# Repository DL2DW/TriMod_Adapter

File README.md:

# TriMod Adapter

## IEEE-488 for the Commodore 1541 Disk Drive

With the help of this adapter, you can turn a VC1541 into a 2031LP in no time. And it is just as easy to switch back again.

So to speak, the best of two different worlds. Once the Commodore 1541 with the CBM bus for Commodore C64 and C128. And switchable as 2031LP for the PET and CBM world with GPIB (IEEE-488) interface.

The idea came from Andre Fachat and was published in 64'er magazine in the 1980s. He was the first to come up with the idea of turning a 1541 into a 2031LP.

I took up this idea again and even made the whole thing switchable. So you can always use the "1541 mode" again without removing the adapter again.

# Technical

Commodore had derived the 2031LP from the 1541 at that time. If you look at both schematics, they only differ in one detail.

And this is the connection to the outside world. 

On the 1541, the VIA 6522 is only partially used, because port A is not connected. Port B provides the lines for the CBM bus, which communicate with the computer via a 74LS14 and 74LS06 driver.

In contrast, port A is also required for the 2031LP. This provides the 8 parallel data lines, while port B is responsible for the control lines of the GPIB bus. Here the two drivers SN75160 and SN75161 are used.

And these are basically the actual differences, to put it simply.

So the 1541 can be easily converted to a 2031 with an adapter board. Of course, the Kernal has to be exchanged accordingly.

So that the adapter does not have to be removed every time you want to use the CBM bus, I have made the whole switchable.

With the help of CD4066 4-fold switches, the lines can be easily switched. At the same time the integrated Kernal adapter is also switched.

A 27128 EPROM is required for the Kernal. First (address 0x0000) the binary for the 1541 mode is written and afterwards (address 0x2000) the binary for the IEEE-488 mode.

With setting the jumper the mode can be switched. Of course this should be done only in the switched off state.

# BOM

Here is the list of components. 

|      | Description                                                  | Part                  | References           | Value                       | Quantity Per PCB |
| ---- | ------------------------------------------------------------ | --------------------- | -------------------- | --------------------------- | ---------------- |
| 1    | Unpolarized capacitor                                        | C                     | C1 C2 C3 C4 C5 C6 C7 | 100nF                       | 7                |
| 2    | Diode                                                        | D                     | D1 D2                | 1N4148                      | 2                |
| 3    | Generic connector, single row, 01x12, script generated (kicad-library-utils/schlib/autogen/connector/) | Conn_01x12            | J4 J5                | Conn_01x12                  | 2                |
| 4    | Generic connector, double row, 02x12, top/bottom pin numbering scheme (row 1: 1...pins_per_row, row2: pins_per_row+1 ... num_pins), script generated (kicad-library-utils/schlib/autogen/connector/) | Conn_02x12_Top_Bottom | J3                   | IEEE-488 Connector          | 1                |
| 5    | Generic connector, single row, 01x20, script generated (kicad-library-utils/schlib/autogen/connector/) | Conn_01x20            | J1 J2                | PIN Header to PCB 6522 1-20 | 2                |
| 6    | Jumper, 2-pole, open                                         | Jumper_2_Open         | JP1                  | Jumper                      | 1                |
| 7    | Resistor                                                     | R                     | R1 R4                | 10k                         | 2                |
| 8    | Resistor                                                     | R                     | R5                   | 1k                          | 1                |
| 9    | Resistor                                                     | R                     | R2 R3 R6             | 3k3                         | 3                |
| 10   | 2x DIP Switch, Single Pole Single Throw (SPST) switch, small symbol | SW_DIP_x02            | SW1                  | IEEE-488 Device ID          | 1                |
| 11   | OTP EPROM 128 KiBit, [Obsolete 2004-01]                      | 27C128                | U8                   | 27C128                      | 1                |
| 12   | Quad Analog Switches                                         | 4066                  | U1 U2                | 4066                        | 2                |
| 13   |                                                              | 7406N                 | U4                   | 7406N                       | 1                |
| 14   | Quad 2-input XOR                                             | 74LS86                | U3                   | 74LS86                      | 1                |
| 15   |                                                              | MOS6522               | U5                   | MOS6522                     | 1                |
| 16   |                                                              | SN75160               | U6                   | SN75160                     | 1                |
| 17   |                                                              | SN75161               | U7                   | SN75161                     | 1                |

# PCB

The PCB can either be ordered directly from [PCBWay](https://www.pcbway.com/project/shareproject/TriMod_Adapter.html), or you can create it yourself from the Gerber files available here.

If you liked my project, I would be very happy about a small coffee donation.

# License

The contents of this repository, with the exception of the Docs and Software directories, are released under the following license:

- the "Creative Commons Attribution-NonCommercial-ShareAlike 4.0 International License" (CC BY-NC-SA 4.0) full text of this license is included in the [LICENSE.CC-NC-BY-SA-4.0](https://github.com/DL2DW/TriMod_Adapter/blob/main/LICENSE.CC-NC-BY-SA) file and a copy can also be found at https://creativecommons.org/licenses/by-nc-sa/4.0/

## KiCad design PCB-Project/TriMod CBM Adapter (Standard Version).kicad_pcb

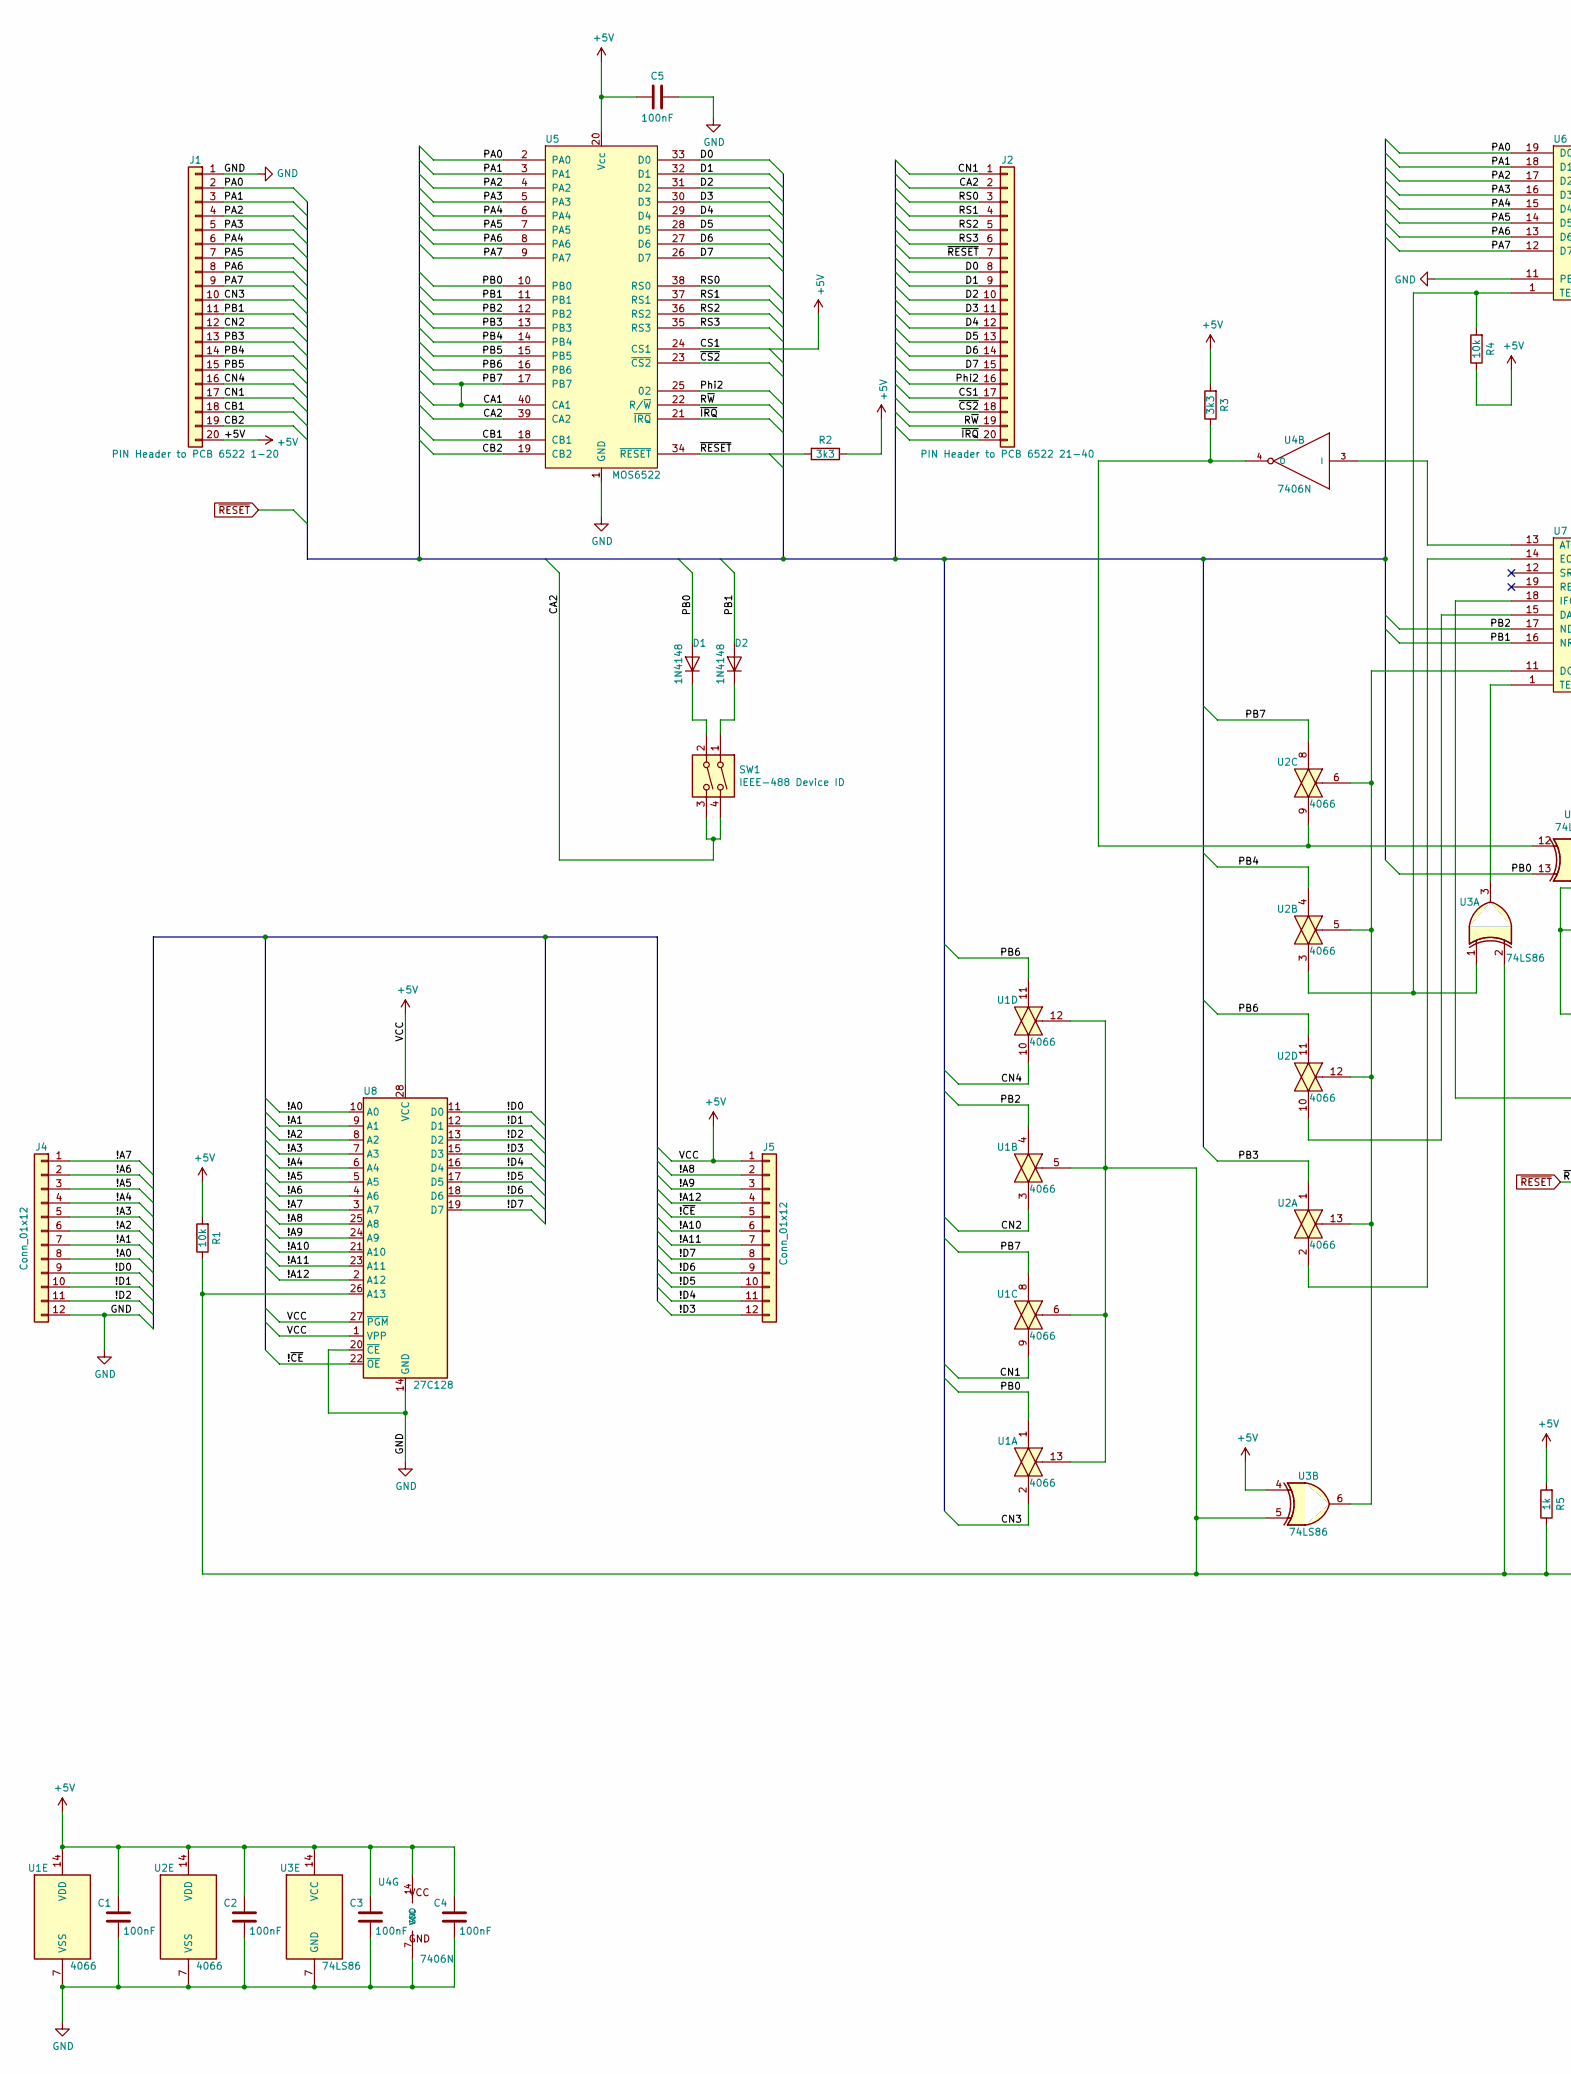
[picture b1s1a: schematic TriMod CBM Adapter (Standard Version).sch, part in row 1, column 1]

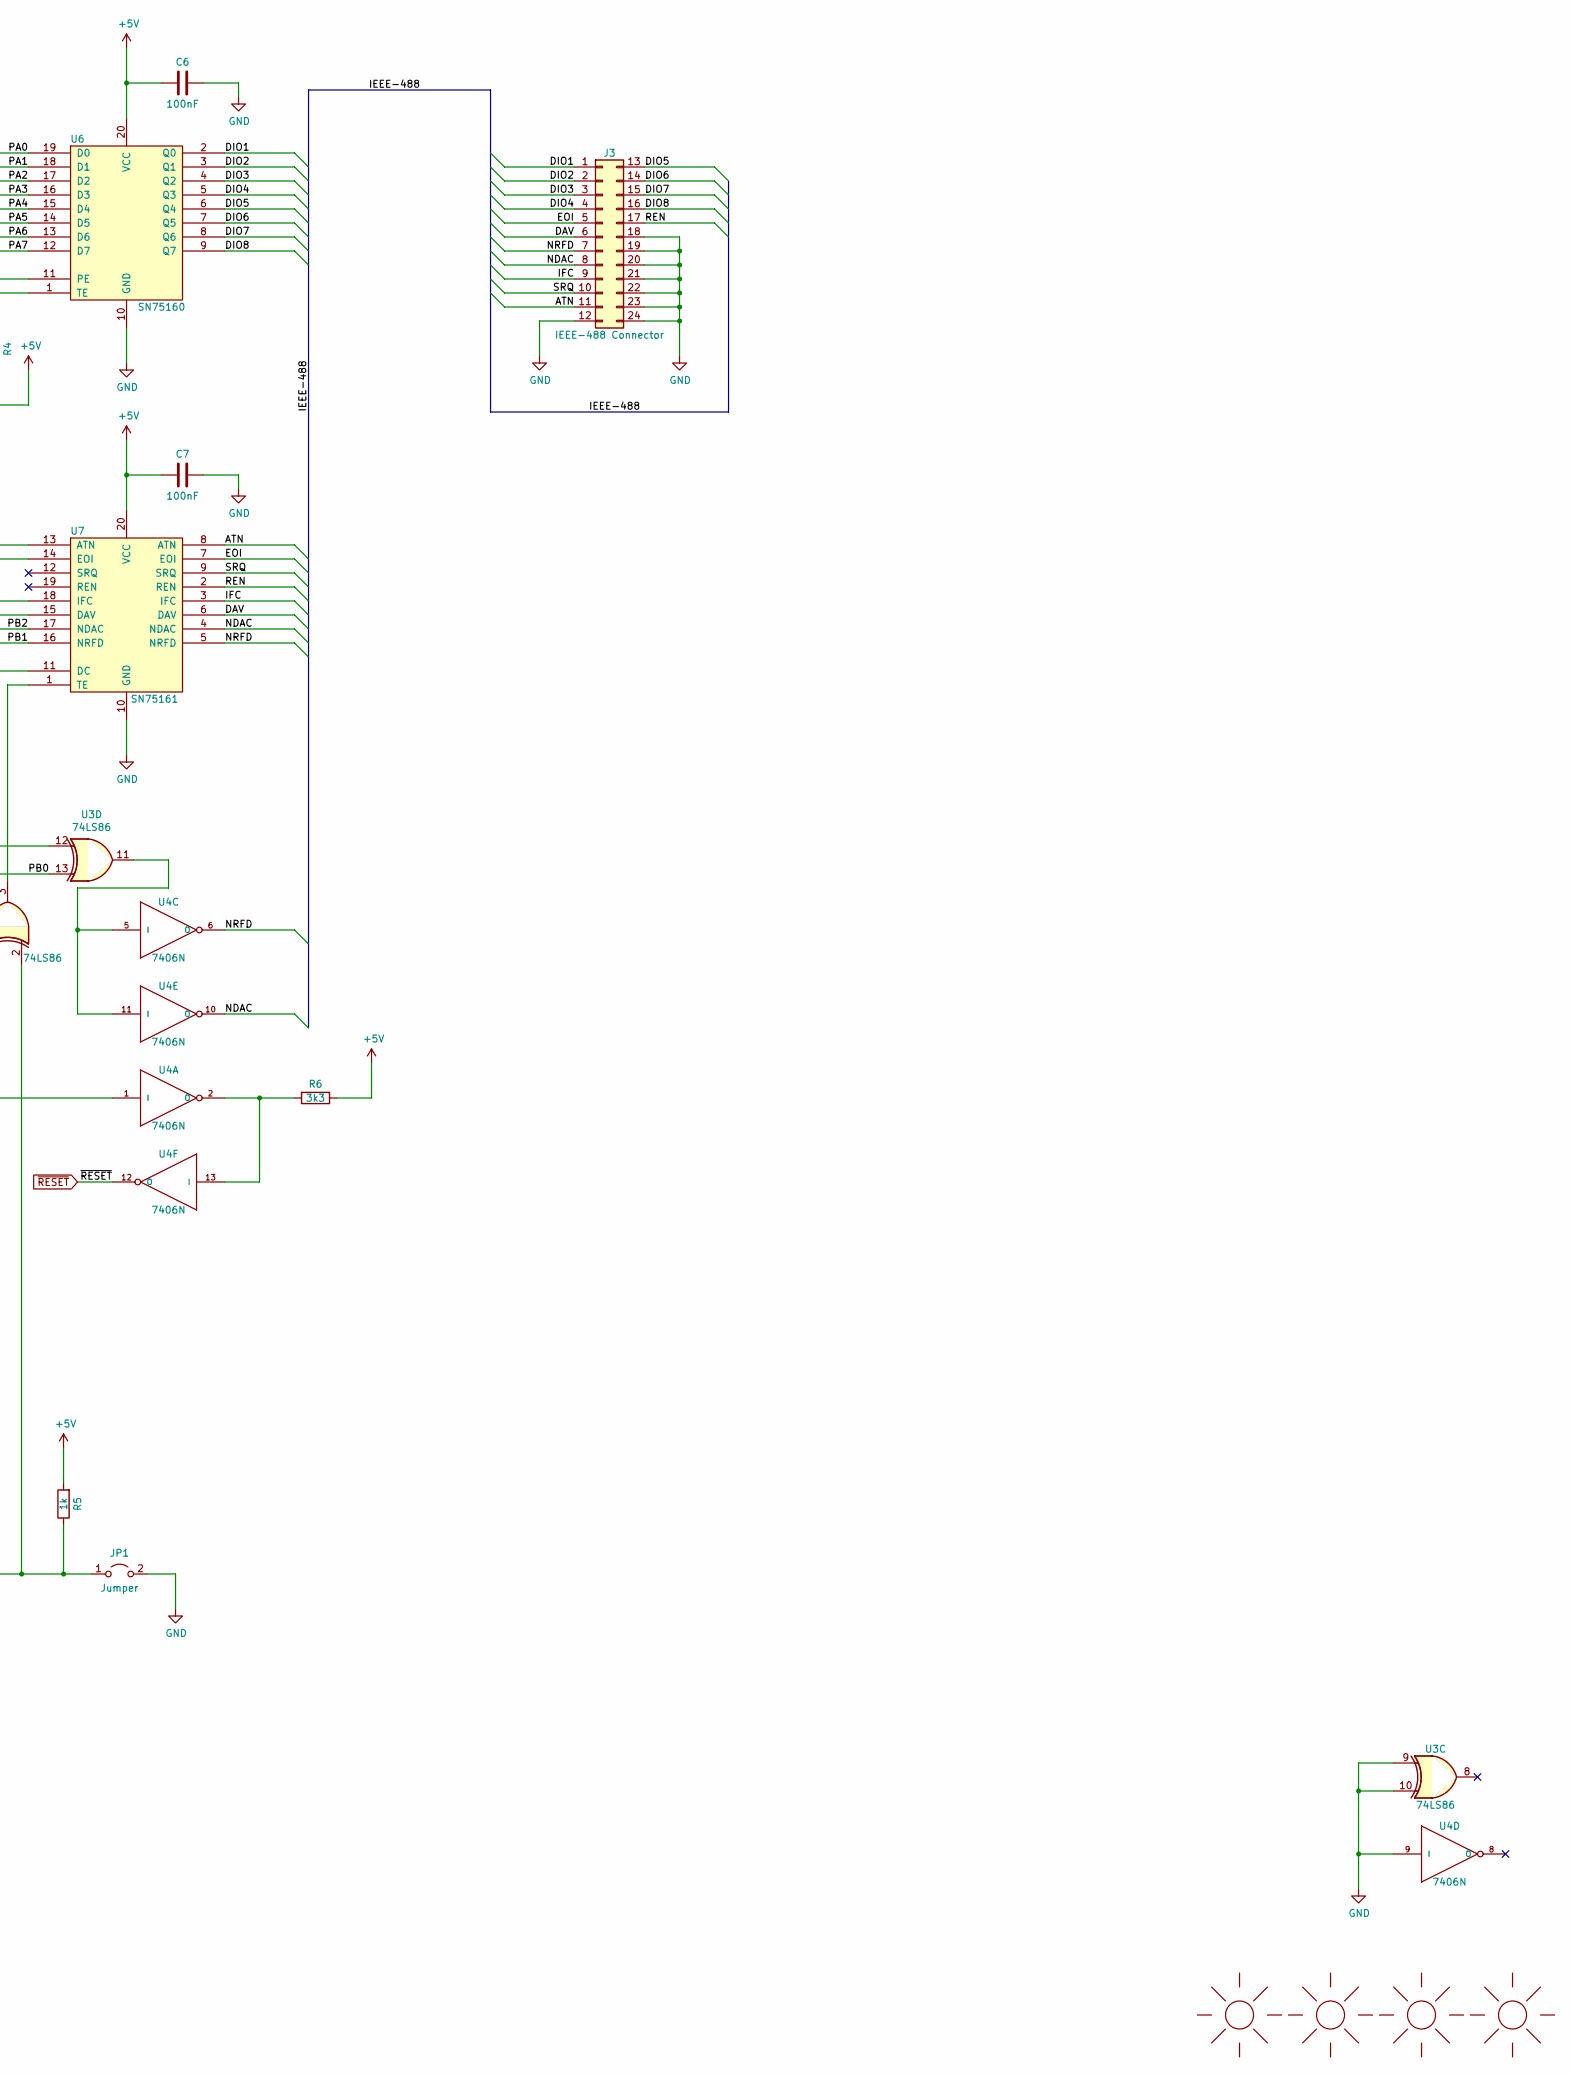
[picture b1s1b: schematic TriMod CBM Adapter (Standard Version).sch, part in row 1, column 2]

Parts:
C1, C2, C3, C4, C5, C6, C7: 100nF; C_Disc_D3.4mm_W2.1mm_P2.50mm
D1, D2: 1N4148; D_DO-35_SOD27_P7.62mm_Horizontal
J1: PIN Header to PCB 6522 1-20; PinHeader_1x20_P2.54mm_Vertical
J2: PIN Header to PCB 6522 21-40; PinHeader_1x20_P2.54mm_Vertical
J3: IEEE-488 Connector; IDC-Header_IEEE-488_2x12_P2.54mm_Horizontal
J4, J5: Conn_01x12; PinHeader_1x12_P2.54mm_Vertical
JP1: Jumper; PinHeader_1x02_P2.54mm_Vertical
M1: SUNLOGO; DL2DW_Logo_Silk_20x10mm
M2: SUNLOGO; KiCad-Logo2_8mm_SilkScreen
M3: SUNLOGO; Logo_silk_OSHW_6x6mm
M4: SUNLOGO; Logo_silk_CC-BY-NC-SA_10x3.6mm
R1, R4: 10k; R_Axial_DIN0207_L6.3mm_D2.5mm_P7.62mm_Horizontal
R2, R3, R6: 3k3; R_Axial_DIN0207_L6.3mm_D2.5mm_P7.62mm_Horizontal
R5: 1k; R_Axial_DIN0207_L6.3mm_D2.5mm_P7.62mm_Horizontal
SW1: IEEE-488 Device ID; SW_DIP_SPSTx02_Slide_9.78x7.26mm_W7.62mm_P2.54mm
U1, U2: 4066; dil_14-300_socket
U3: 74LS86; dil_14-300_socket
U4: 7406N; dil_14-300_socket
U5: MOS6522; dil_40-600_socket
U6: SN75160; dil_20-300_socket
U7: SN75161; dil_20-300_socket
U8: 27C128; dil_28-600_socket

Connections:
+5V: C1.2, C2.2, C3.2, C4.2, C5.2, C6.2, C7.2, J1.20, J2.17, J5.1, R1.2, R2.1, R3.2, R4.1, R5.2, R6.1, U1.14 (VDD), U2.14 (VDD), U3.4, U3.14 (VCC), U4.14 (VCC), U5.20 (Vcc), U5.24 (CS1), U6.20 (VCC), U7.20 (VCC), U8.1 (VPP), U8.27 (~PGM), U8.28 (VCC)
/!A0: J4.8, U8.10 (A0)
/!A1: J4.7, U8.9 (A1)
/!A2: J4.6, U8.8 (A2)
/!A3: J4.5, U8.7 (A3)
/!A4: J4.4, U8.6 (A4)
/!A5: J4.3, U8.5 (A5)
/!A6: J4.2, U8.4 (A6)
/!A7: J4.1, U8.3 (A7)
/!A8: J5.2, U8.25 (A8)
/!A9: J5.3, U8.24 (A9)
/!A10: J5.6, U8.21 (A10)
/!A11: J5.7, U8.23 (A11)
/!A12: J5.4, U8.2 (A12)
/!D0: J4.9, U8.11 (D0)
/!D1: J4.10, U8.12 (D1)
/!D2: J4.11, U8.13 (D2)
/!D3: J5.12, U8.15 (D3)
/!D4: J5.11, U8.16 (D4)
/!D5: J5.10, U8.17 (D5)
/!D6: J5.9, U8.18 (D6)
/!D7: J5.8, U8.19 (D7)
/!~CE: J5.5, U8.22 (~OE)
/ATN: J3.11, U7.8 (ATN)
/CA1: U1.8, U2.8, U5.17 (PB7), U5.40 (CA1)
/CA2: J2.2, SW1.3, SW1.4, U5.39 (CA2)
/CB1: J1.18, U5.18 (CB1)
/CB2: J1.19, U5.19 (CB2)
/CN1: J1.17, J2.1, U1.9
/CN2: J1.12, U1.3
/CN3: J1.10, U1.2
/CN4: J1.16, U1.10
/D0: J2.8, U5.33 (D0)
/D1: J2.9, U5.32 (D1)
/D2: J2.10, U5.31 (D2)
/D3: J2.11, U5.30 (D3)
/D4: J2.12, U5.29 (D4)
/D5: J2.13, U5.28 (D5)
/D6: J2.14, U5.27 (D6)
/D7: J2.15, U5.26 (D7)
/DAV: J3.6, U7.6 (DAV)
/DIO1: J3.1, U6.2 (Q0)
/DIO2: J3.2, U6.3 (Q1)
/DIO3: J3.3, U6.4 (Q2)
/DIO4: J3.4, U6.5 (Q3)
/DIO5: J3.13, U6.6 (Q4)
/DIO6: J3.14, U6.7 (Q5)
/DIO7: J3.15, U6.8 (Q6)
/DIO8: J3.16, U6.9 (Q7)
/EOI: J3.5, U7.7 (EOI)
/IFC: J3.9, U7.3 (IFC)
/NDAC: J3.8, U4.10 (O), U7.4 (NDAC)
/NRFD: J3.7, U4.6 (O), U7.5 (NRFD)
/PA0: J1.2, U5.2 (PA0), U6.19 (D0)
/PA1: J1.3, U5.3 (PA1), U6.18 (D1)
/PA2: J1.4, U5.4 (PA2), U6.17 (D2)
/PA3: J1.5, U5.5 (PA3), U6.16 (D3)
/PA4: J1.6, U5.6 (PA4), U6.15 (D4)
/PA5: J1.7, U5.7 (PA5), U6.14 (D5)
/PA6: J1.8, U5.8 (PA6), U6.13 (D6)
/PA7: J1.9, U5.9 (PA7), U6.12 (D7)
/PB0: D1.2 (A), U1.1, U3.13, U5.10 (PB0)
/PB1: D2.2 (A), J1.11, U5.11 (PB1), U7.16 (NRFD)
/PB2: U1.4, U5.12 (PB2), U7.17 (NDAC)
/PB3: J1.13, U2.1, U5.13 (PB3)
/PB4: J1.14, U2.4, U5.14 (PB4)
/PB5: J1.15, U5.15 (PB5)
/PB6: U1.11, U2.11, U5.16 (PB6)
/Phi2: J2.16, U5.25 (02)
/REN: J3.17, U7.2 (REN)
/RS0: J2.3, U5.38 (RS0)
/RS1: J2.4, U5.37 (RS1)
/RS2: J2.5, U5.36 (RS2)
/RS3: J2.6, U5.35 (RS3)
/R~W: J2.19, U5.22 (R/~W)
/SRQ: J3.10, U7.9 (SRQ)
/~CS2: J2.18, U5.23 (~CS2)
/~IRQ: J2.20, U5.21 (~IRQ)
GND: C1.1, C2.1, C3.1, C4.1, C5.1, C6.1, C7.1, J1.1, J3.12, J3.18, J3.19, J3.20, J3.21, J3.22, J3.23, J3.24, J4.12, JP1.2 (B), U1.7 (VSS), U2.7 (VSS), U3.7 (GND), U3.9, U3.10, U4.7 (GND), U4.9 (I), U5.1 (GND), U6.10 (GND), U6.11 (PE), U7.10 (GND), U8.14 (GND), U8.20 (~CE)
unnamed: D1.1 (K), SW1.2
unnamed: D2.1 (K), SW1.1
unnamed: JP1.1 (A), R1.1, R5.1, U1.5, U1.6, U1.12, U1.13, U3.2, U3.5, U8.26 (A13)
unnamed: R3.1, U2.9, U3.12, U4.4 (O)
unnamed: R4.2, U2.3, U3.1, U6.1 (TE)
unnamed: R6.2, U4.2 (O), U4.13 (I)
unnamed: U2.2, U7.14 (EOI)
unnamed: U2.10, U7.15 (DAV)
unnamed: U2.5, U2.6, U2.12, U2.13, U3.6, U7.11 (DC)
unnamed: U3.3, U7.1 (TE)
unnamed: U3.11, U4.5 (I), U4.11 (I)
unnamed: U4.1 (I), U7.18 (IFC)
unnamed: U4.3 (I), U7.13 (ATN)
~RESET: J2.7, R2.2, U4.12 (O), U5.34 (~RESET)

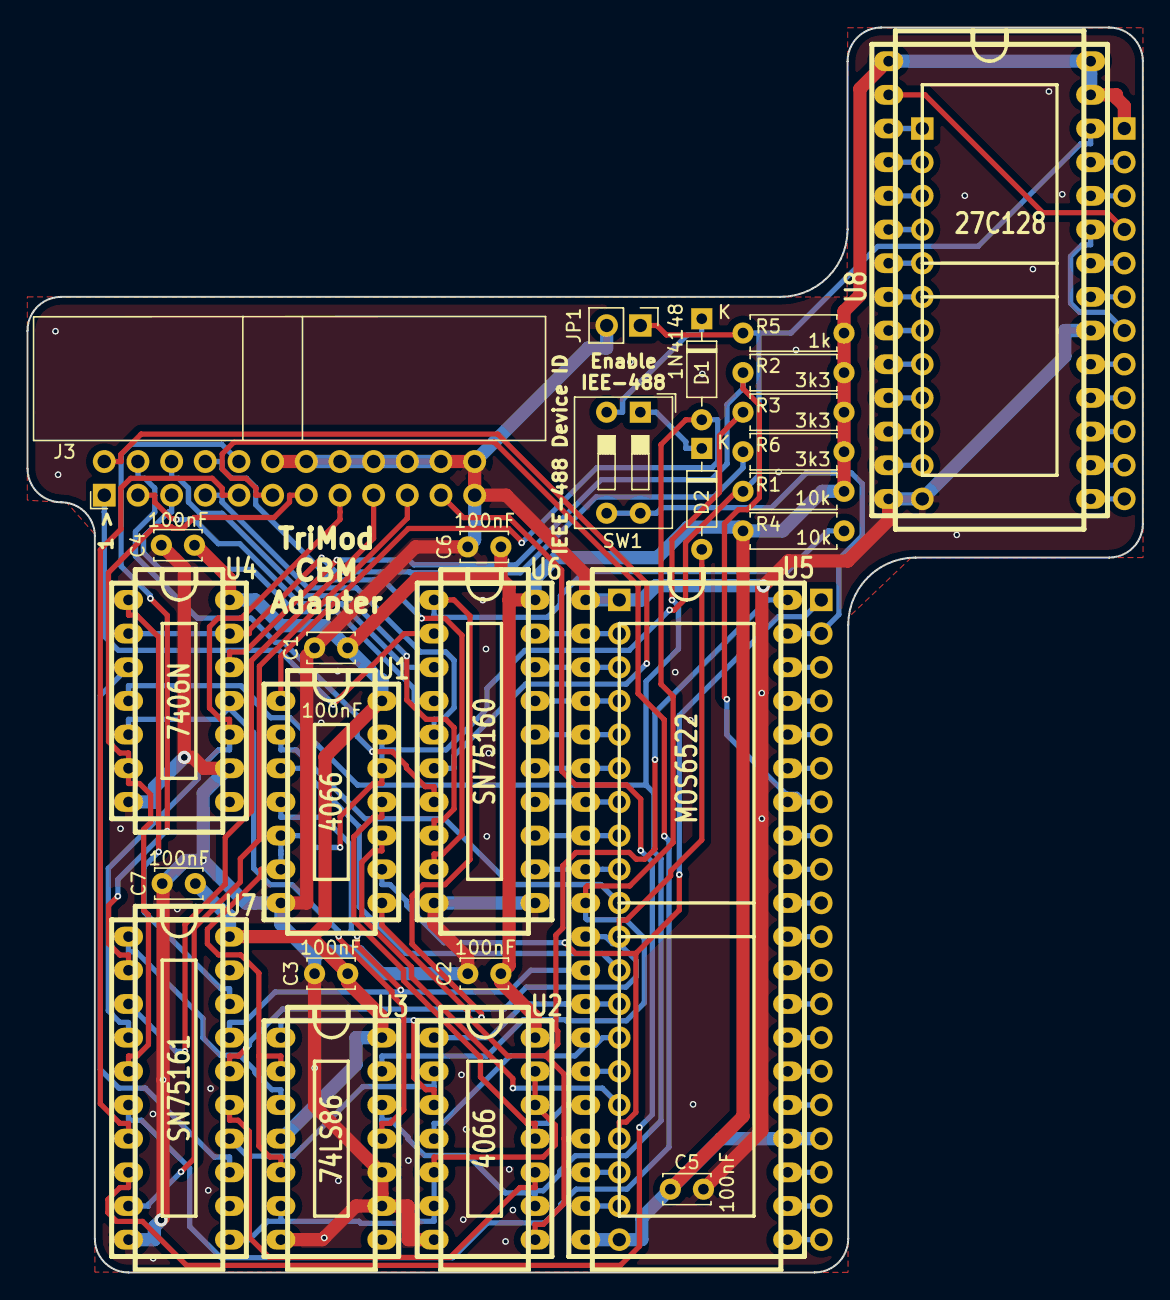
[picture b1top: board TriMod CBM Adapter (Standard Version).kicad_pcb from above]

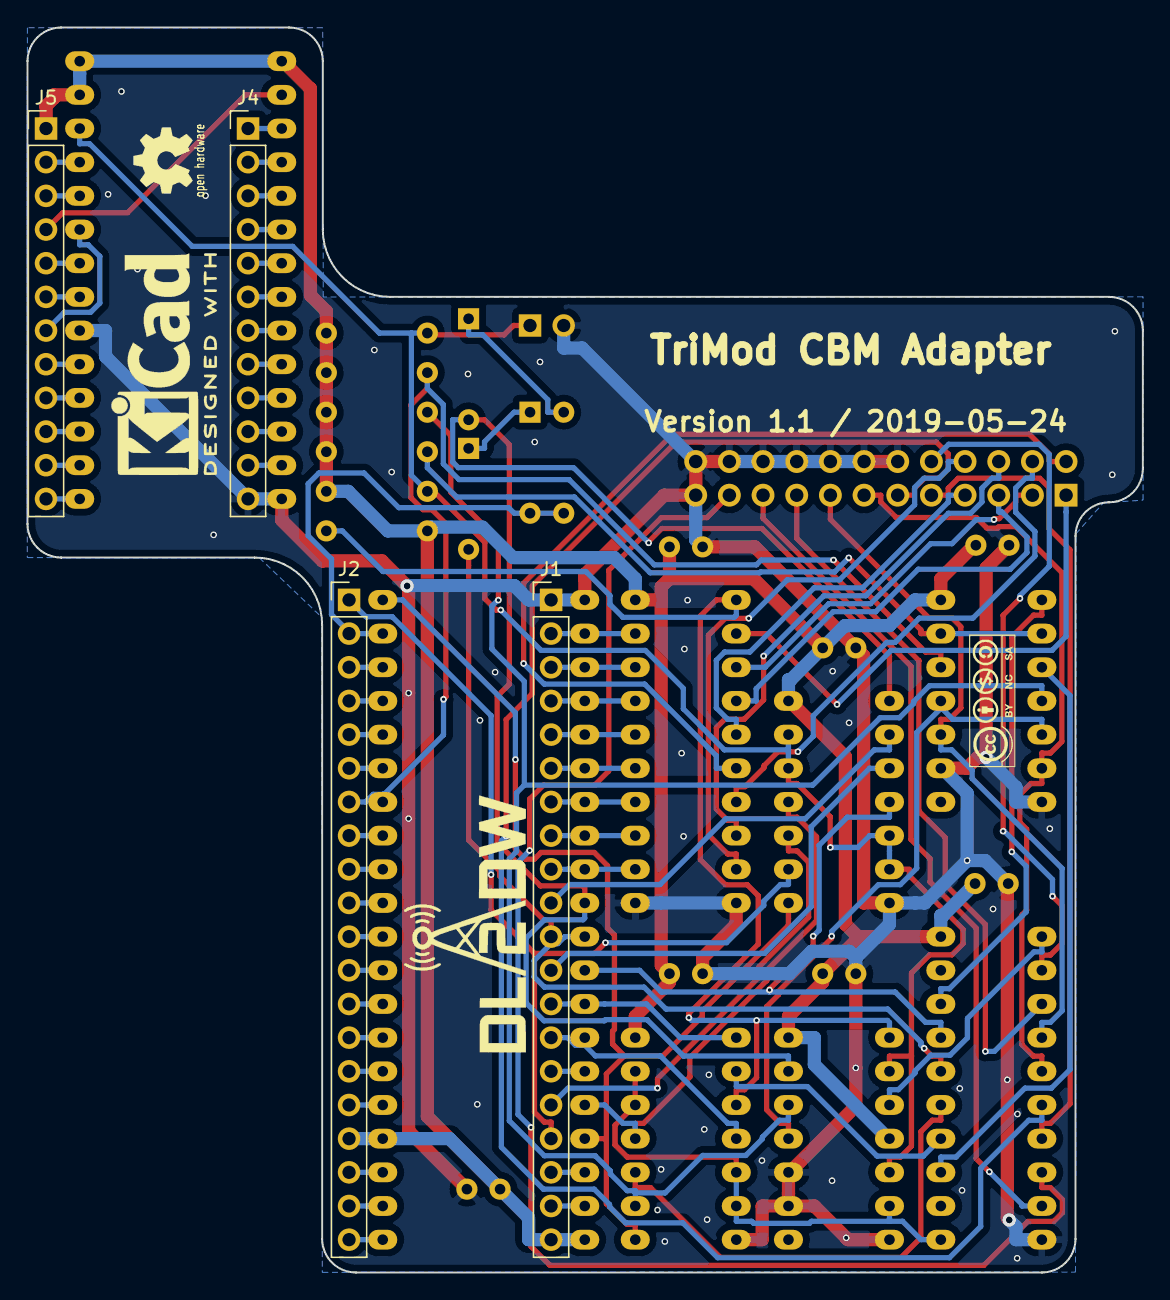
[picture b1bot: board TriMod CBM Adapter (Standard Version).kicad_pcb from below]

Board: 2 copper layers, 84.1 x 93.9 mm, 34 parts (8 on the bottom side), 93 nets.

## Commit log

2021-01-07 PCB order link added
